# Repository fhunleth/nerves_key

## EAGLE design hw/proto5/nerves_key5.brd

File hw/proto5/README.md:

This version has big holes as an experiment to see whether it makes soldering
to the bottom of an existing header easier.

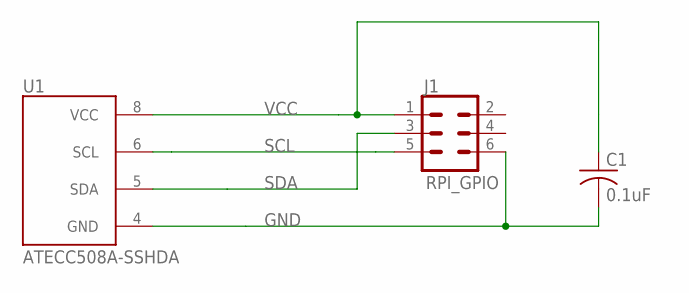
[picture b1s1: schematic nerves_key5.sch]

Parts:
C1: 0.1uF; C0603
J1: RPI_GPIO; 2X3_BIG_HOLES
U1: ATECC508A-SSHDA; SOIC127P625X175-8

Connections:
GND: C1.2, J1.6, U1.4 (GND)
SCL: J1.5, U1.6 (SCL)
SDA: J1.3, U1.5 (SDA)
VCC: C1.1, J1.1, U1.8 (VCC)

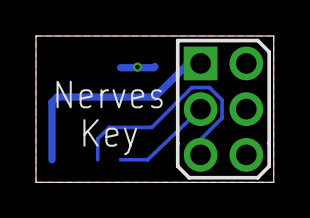
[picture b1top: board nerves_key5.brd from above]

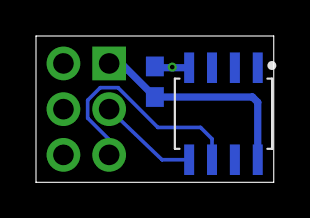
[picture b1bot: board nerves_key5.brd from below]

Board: 2 copper layers, 13.2 x 8.1 mm, 3 parts (2 on the bottom side), 4 nets.

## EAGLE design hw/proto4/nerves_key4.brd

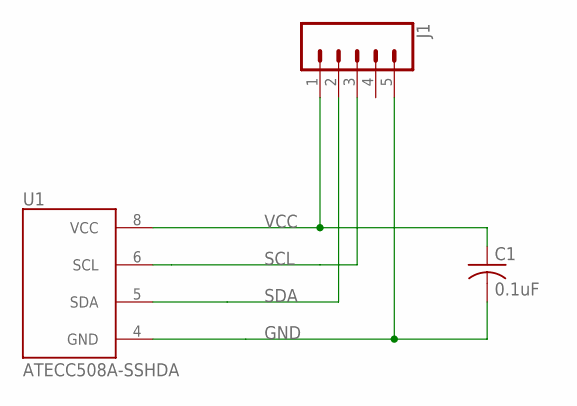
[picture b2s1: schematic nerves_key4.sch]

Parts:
C1: 0.1uF; C0603
J1: CONN_05; 1X05
U1: ATECC508A-SSHDA; SOIC127P625X175-8

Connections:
GND: C1.2, J1.5, U1.4 (GND)
SCL: J1.3, U1.6 (SCL)
SDA: J1.2, U1.5 (SDA)
VCC: C1.1, J1.1, U1.8 (VCC)

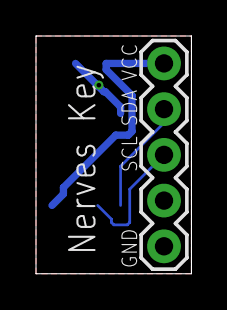
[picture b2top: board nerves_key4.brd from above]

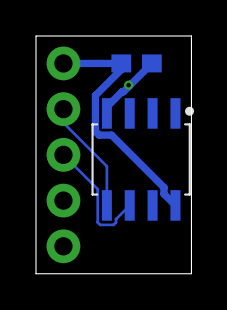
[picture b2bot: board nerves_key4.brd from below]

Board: 2 copper layers, 8.6 x 13.2 mm, 3 parts (2 on the bottom side), 4 nets.

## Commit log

2018-09-02 Add version with components on bottom
2018-09-02 Add 5x1 version
2018-09-03 Save 5 cents
2018-09-03 Fix ERC/DRC
2018-09-03 Add big hole experiment
2018-09-03 Ignore Eagle temp files

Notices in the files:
parts and their libraries:
SparkFun-Connectors: Licensing: Creative Commons ShareAlike 4.0 International - https://creativecommons.org/licenses/by-sa/4.0
